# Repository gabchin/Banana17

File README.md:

# Banana17
An RP2040 numpad running QMK

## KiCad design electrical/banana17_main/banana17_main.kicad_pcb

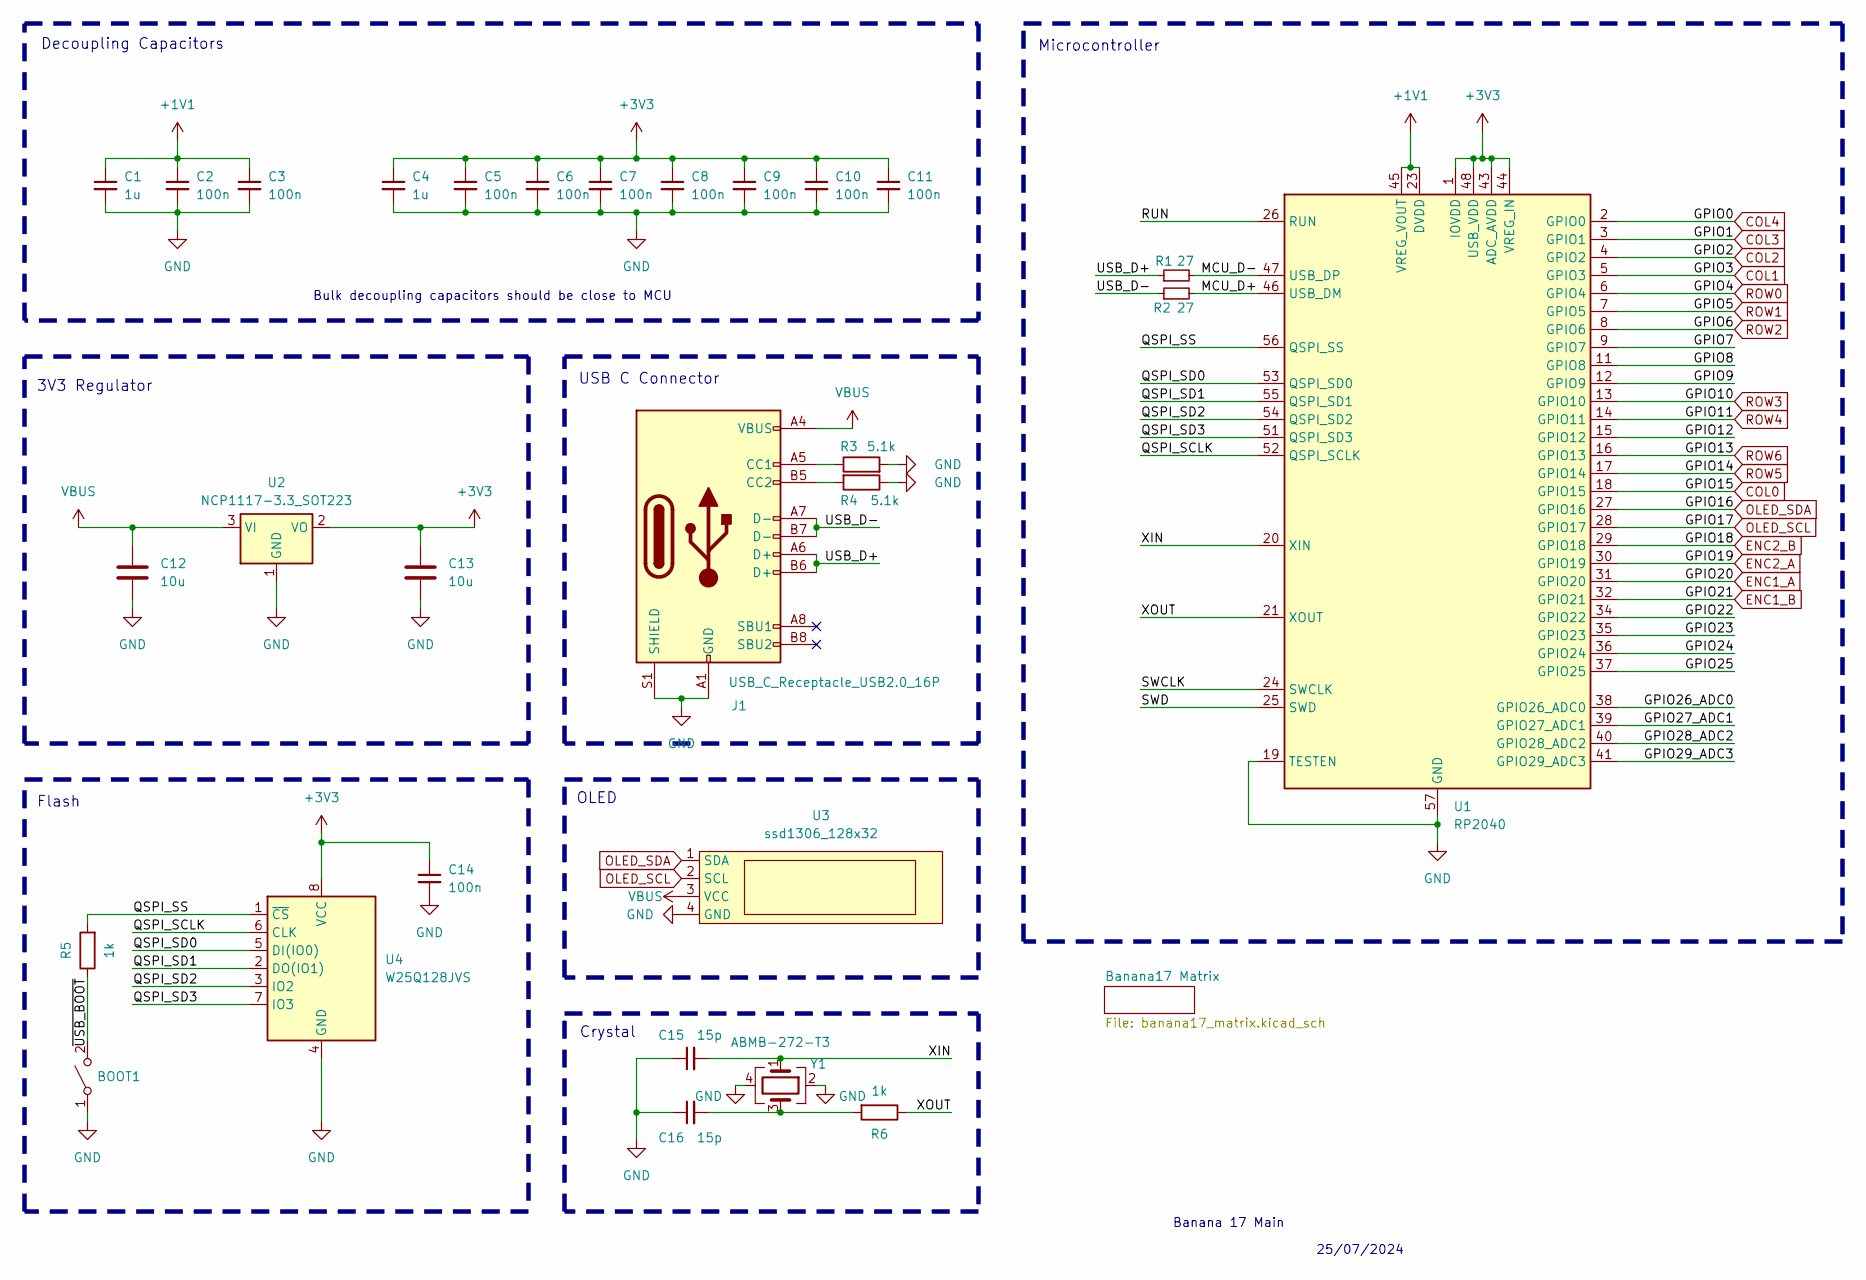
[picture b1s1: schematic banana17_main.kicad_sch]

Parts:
BOOT1: SW_SPST; SW_SPST_PTS810
C1, C4: 1u; C_0402_1005Metric_Pad0.74x0.62mm_HandSolder
C2, C3, C5, C6, C7, C8, C9, C10, C11, C14: 100n; C_0402_1005Metric_Pad0.74x0.62mm_HandSolder
C12, C13: 10u; C_0402_1005Metric_Pad0.74x0.62mm_HandSolder
C15, C16: 15p; C_0402_1005Metric_Pad0.74x0.62mm_HandSolder
J1: USB_C_Receptacle_USB2.0_16P; HRO-TYPE-C-31-M-12-Assembly
R1, R2: 27; R_0402_1005Metric_Pad0.72x0.64mm_HandSolder
R3, R4: 5.1k; R_0402_1005Metric_Pad0.72x0.64mm_HandSolder
R5, R6: 1k; R_0402_1005Metric_Pad0.72x0.64mm_HandSolder
U1: RP2040; QFN-56-1EP_7x7mm_P0.4mm_EP3.2x3.2mm
U2: NCP1117-3.3_SOT223; SOT-223-3_TabPin2
U3: ssd1306_128x32
U4: W25Q128JVS; SOIC-8_5.23x5.23mm_P1.27mm
Y1: ABMB-272-T3; Crystal_SMD_Abracon_ABM8G-4Pin_3.2x2.5mm

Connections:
+1V1: C1.1, C2.1, C3.1, U1.23 (DVDD), U1.45 (VREG_VOUT), U1.50 (DVDD)
+3V3: C4.1, C5.1, C6.1, C7.1, C8.1, C9.1, C10.1, C11.1, C13.1, C14.1, U1.1 (IOVDD), U1.10 (IOVDD), U1.22 (IOVDD), U1.33 (IOVDD), U1.42 (IOVDD), U1.43 (ADC_AVDD), U1.44 (VREG_IN), U1.48 (USB_VDD), U1.49 (IOVDD), U2.2 (VO), U4.8 (VCC)
/GPIO7: U1.9 (GPIO7)
/GPIO8: U1.11 (GPIO8)
/GPIO9: U1.12 (GPIO9)
/GPIO12: U1.15 (GPIO12)
/GPIO22: U1.34 (GPIO22)
/GPIO23: U1.35 (GPIO23)
/GPIO24: U1.36 (GPIO24)
/GPIO25: U1.37 (GPIO25)
/GPIO26_ADC0: U1.38 (GPIO26_ADC0)
/GPIO27_ADC1: U1.39 (GPIO27_ADC1)
/GPIO28_ADC2: U1.40 (GPIO28_ADC2)
/GPIO29_ADC3: U1.41 (GPIO29_ADC3)
/MCU_D+: R2.2, U1.46 (USB_DM)
/MCU_D-: R1.2, U1.47 (USB_DP)
/QSPI_SCLK: U1.52 (QSPI_SCLK), U4.6 (CLK)
/QSPI_SD0: U1.53 (QSPI_SD0), U4.5 (DI(IO0))
/QSPI_SD1: U1.55 (QSPI_SD1), U4.2 (DO(IO1))
/QSPI_SD2: U1.54 (QSPI_SD2), U4.3 (IO2)
/QSPI_SD3: U1.51 (QSPI_SD3), U4.7 (IO3)
/QSPI_SS: R5.2, U1.56 (QSPI_SS), U4.1 (~CS)
/RUN: U1.26 (RUN)
/SWCLK: U1.24 (SWCLK)
/SWD: U1.25 (SWD)
/USB_D+: J1.A6 (D+), J1.B6 (D+), R1.1
/USB_D-: J1.A7 (D-), J1.B7 (D-), R2.1
/XIN: C15.2, U1.20 (XIN), Y1.1
/XOUT: R6.1, U1.21 (XOUT)
/~USB_BOOT: BOOT1.2 (B), R5.1
COL0: U1.18 (GPIO15); also elsewhere on the board
COL1: U1.5 (GPIO3); also elsewhere on the board
COL2: U1.4 (GPIO2); also elsewhere on the board
COL3: U1.3 (GPIO1); also elsewhere on the board
COL4: U1.2 (GPIO0); also elsewhere on the board
ENC1_A: U1.31 (GPIO20); also elsewhere on the board
ENC1_B: U1.32 (GPIO21); also elsewhere on the board
ENC2_A: U1.30 (GPIO19); also elsewhere on the board
ENC2_B: U1.29 (GPIO18); also elsewhere on the board
GND: BOOT1.1 (A), C1.2, C2.2, C3.2, C4.2, C5.2, C6.2, C7.2, C8.2, C9.2, C10.2, C11.2, C12.2, C13.2, C14.2, C15.1, C16.1, J1.A1 (GND), J1.A12 (GND), J1.B1 (GND), J1.B12 (GND), J1.S1 (SHIELD), R3.2, R4.1, U1.19 (TESTEN), U1.57 (GND), U2.1 (GND), U3.4 (GND), U4.4 (GND), Y1.2, Y1.4; also elsewhere on the board
unnamed: C16.2, R6.2, Y1.3
unnamed: J1.A5 (CC1), R3.1
unnamed: J1.B5 (CC2), R4.2
OLED_SCL: U1.28 (GPIO17), U3.2 (SCL)
OLED_SDA: U1.27 (GPIO16), U3.1 (SDA)
ROW0: U1.6 (GPIO4); also elsewhere on the board
ROW1: U1.7 (GPIO5); also elsewhere on the board
ROW2: U1.8 (GPIO6); also elsewhere on the board
ROW3: U1.13 (GPIO10); also elsewhere on the board
ROW4: U1.14 (GPIO11); also elsewhere on the board
ROW5: U1.17 (GPIO14); also elsewhere on the board
ROW6: U1.16 (GPIO13); also elsewhere on the board
VBUS: C12.1, J1.A4 (VBUS), J1.A9 (VBUS), J1.B4 (VBUS), J1.B9 (VBUS), U2.3 (VI), U3.3 (VCC)

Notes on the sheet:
OLED
Decoupling Capacitors
25/07/2024
Banana 17 Main
Crystal
Microcontroller
USB C Connector
Bulk decoupling capacitors should be close to MCU
Flash
3V3 Regulator

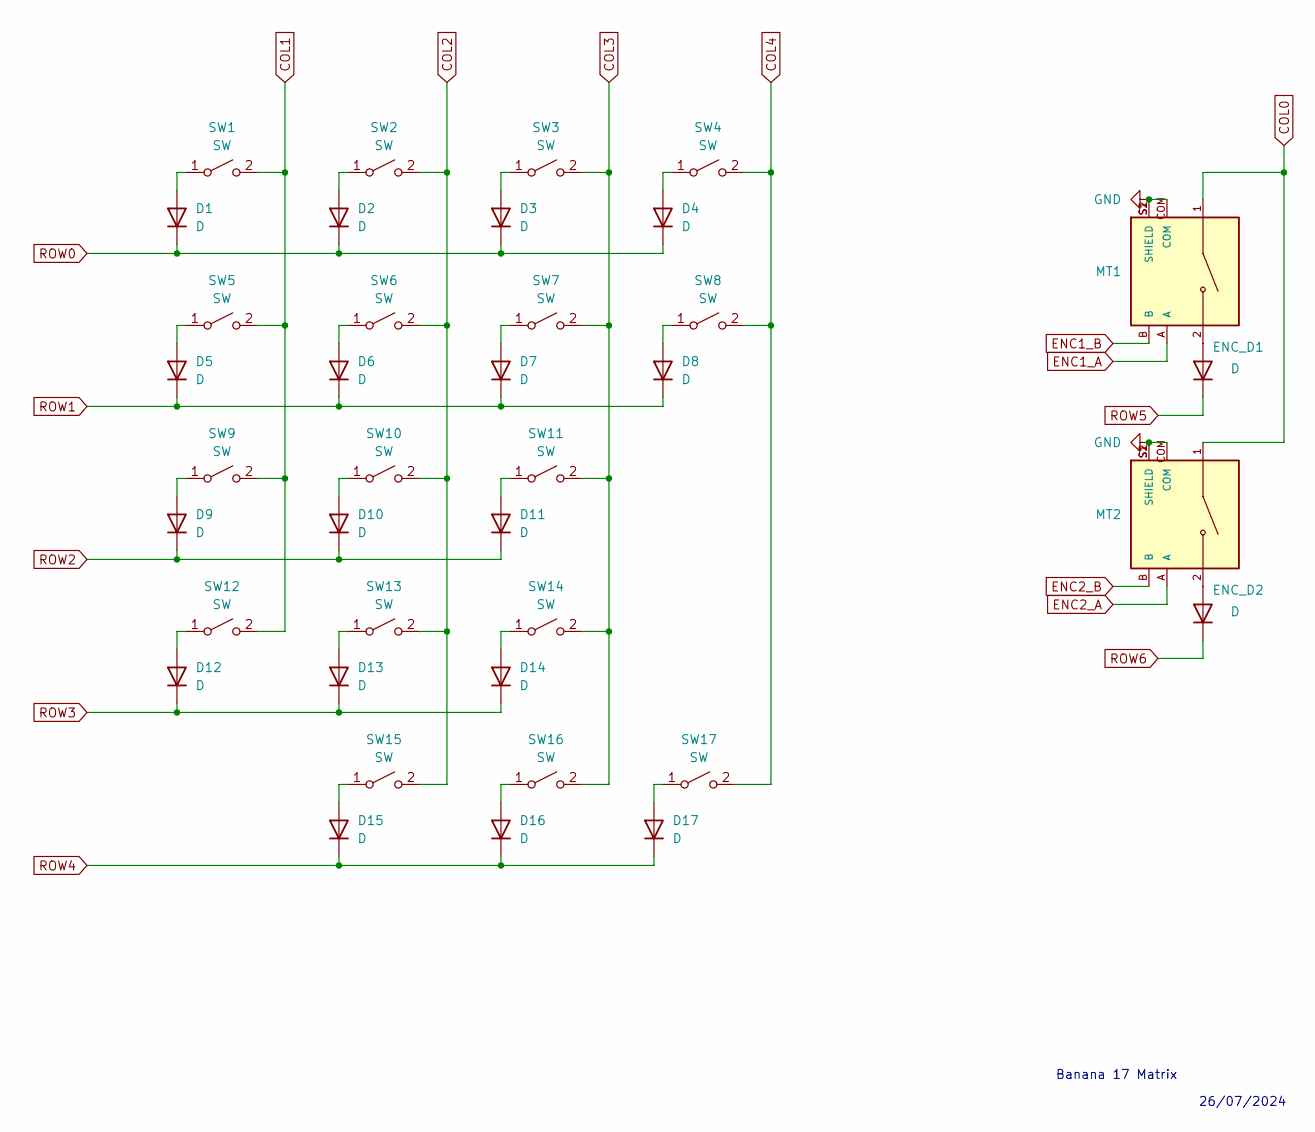
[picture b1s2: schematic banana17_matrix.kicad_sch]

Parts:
D1, D2, D3, D4, D5, D6, D7, D8, D9, D10, D11, D12, D13, D14, D15, D16, D17: D; D_0805_2012Metric_Pad1.15x1.40mm_HandSolder
ENC_D1, ENC_D2: D; D_0805_2012Metric_Pad1.15x1.40mm_HandSolder
MT1, MT2: PEC11R-4215F-S0024; XDCR_PEC11R-4215F-S0024; PARTREV Rev. 09/19
SW1, SW2, SW3, SW4, SW5, SW6, SW7, SW9, SW10, SW11, SW12, SW13, SW14, SW16: SW; MX-Hotswap-1U
SW8, SW17: SW; MX-Hotswap-2U-Vertical
SW15: SW; MX-Hotswap-2U-ReversedStabilizers

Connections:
COL0: MT1.1, MT2.1; also elsewhere on the board
COL1: SW1.2 (B), SW5.2 (B), SW9.2 (B), SW12.2 (B); also elsewhere on the board
COL2: SW2.2 (B), SW6.2 (B), SW10.2 (B), SW13.2 (B), SW15.2 (B); also elsewhere on the board
COL3: SW3.2 (B), SW7.2 (B), SW11.2 (B), SW14.2 (B), SW16.2 (B); also elsewhere on the board
COL4: SW4.2 (B), SW8.2 (B), SW17.2 (B); also elsewhere on the board
ENC1_A: MT1.A; also elsewhere on the board
ENC1_B: MT1.B; also elsewhere on the board
ENC2_A: MT2.A; also elsewhere on the board
ENC2_B: MT2.B; also elsewhere on the board
GND: MT1.COM, MT1.S1 (SHIELD), MT1.S2 (SHIELD), MT2.COM, MT2.S1 (SHIELD), MT2.S2 (SHIELD); also elsewhere on the board
unnamed: D1.2 (A), SW1.1 (A)
unnamed: D2.2 (A), SW2.1 (A)
unnamed: D3.2 (A), SW3.1 (A)
unnamed: D4.2 (A), SW4.1 (A)
unnamed: D5.2 (A), SW5.1 (A)
unnamed: D6.2 (A), SW6.1 (A)
unnamed: D7.2 (A), SW7.1 (A)
unnamed: D8.2 (A), SW8.1 (A)
unnamed: D9.2 (A), SW9.1 (A)
unnamed: D10.2 (A), SW10.1 (A)
unnamed: D11.2 (A), SW11.1 (A)
unnamed: D12.2 (A), SW12.1 (A)
unnamed: D13.2 (A), SW13.1 (A)
unnamed: D14.2 (A), SW14.1 (A)
unnamed: D15.2 (A), SW15.1 (A)
unnamed: D16.2 (A), SW16.1 (A)
unnamed: D17.2 (A), SW17.1 (A)
unnamed: ENC_D1.2 (A), MT1.2
unnamed: ENC_D2.2 (A), MT2.2
ROW0: D1.1 (K), D2.1 (K), D3.1 (K), D4.1 (K); also elsewhere on the board
ROW1: D5.1 (K), D6.1 (K), D7.1 (K), D8.1 (K); also elsewhere on the board
ROW2: D9.1 (K), D10.1 (K), D11.1 (K); also elsewhere on the board
ROW3: D12.1 (K), D13.1 (K), D14.1 (K); also elsewhere on the board
ROW4: D15.1 (K), D16.1 (K), D17.1 (K); also elsewhere on the board
ROW5: ENC_D1.1 (K); also elsewhere on the board
ROW6: ENC_D2.1 (K); also elsewhere on the board

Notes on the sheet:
26/07/2024
Banana 17 Matrix

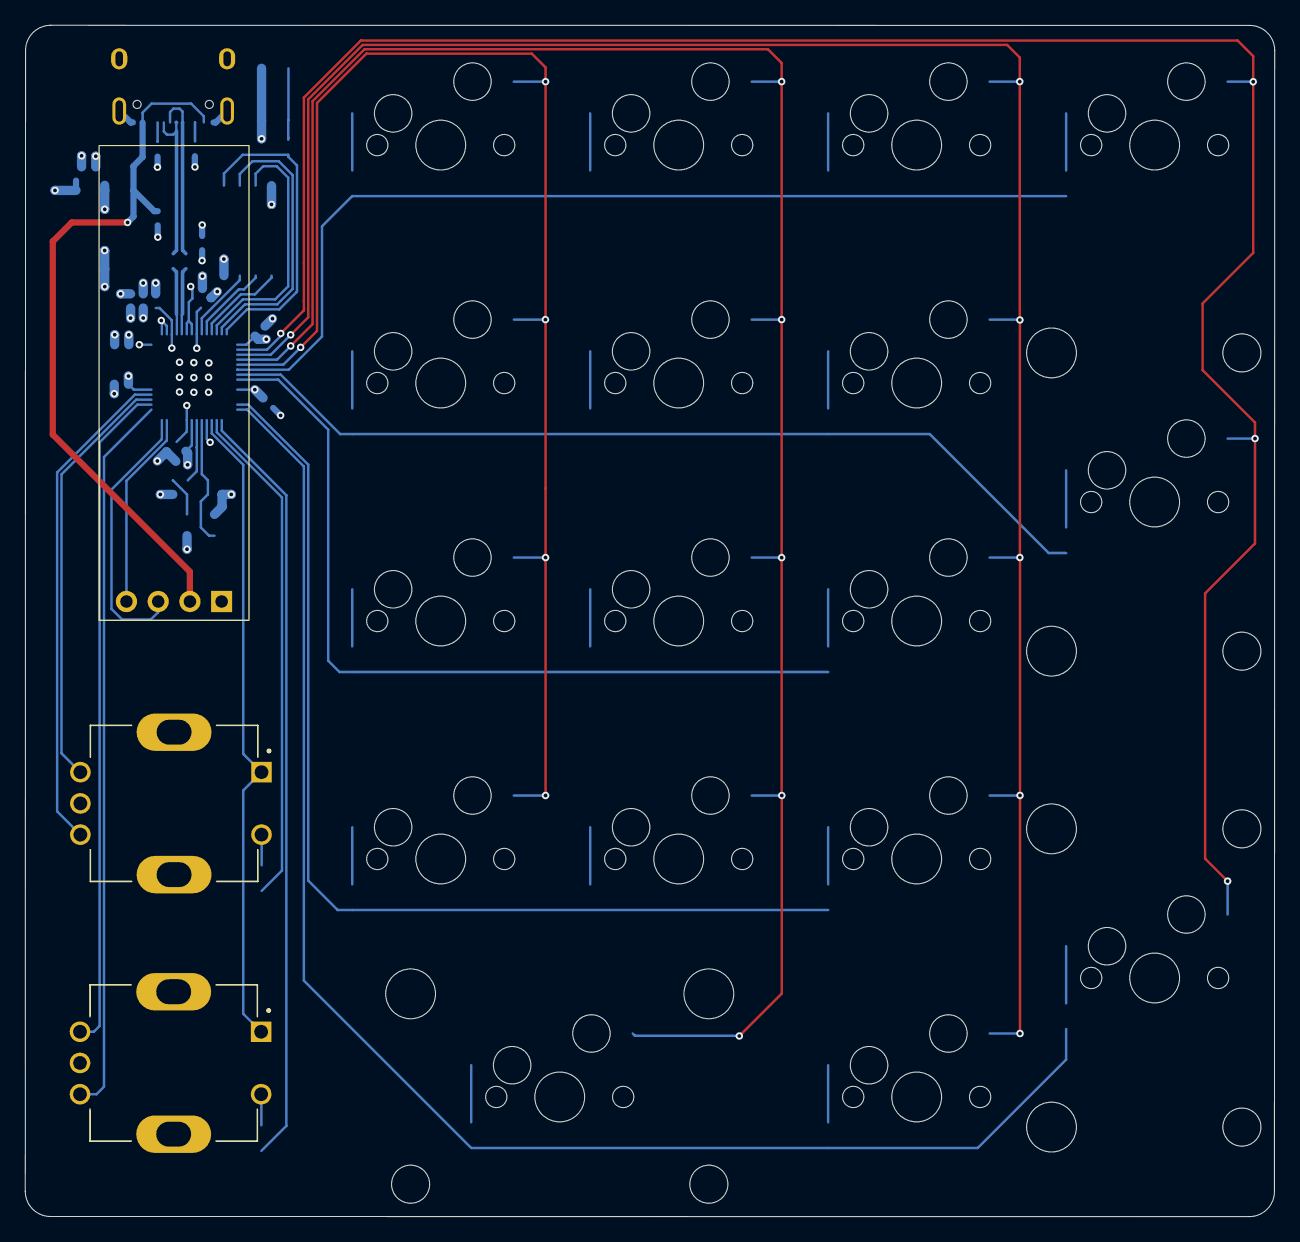
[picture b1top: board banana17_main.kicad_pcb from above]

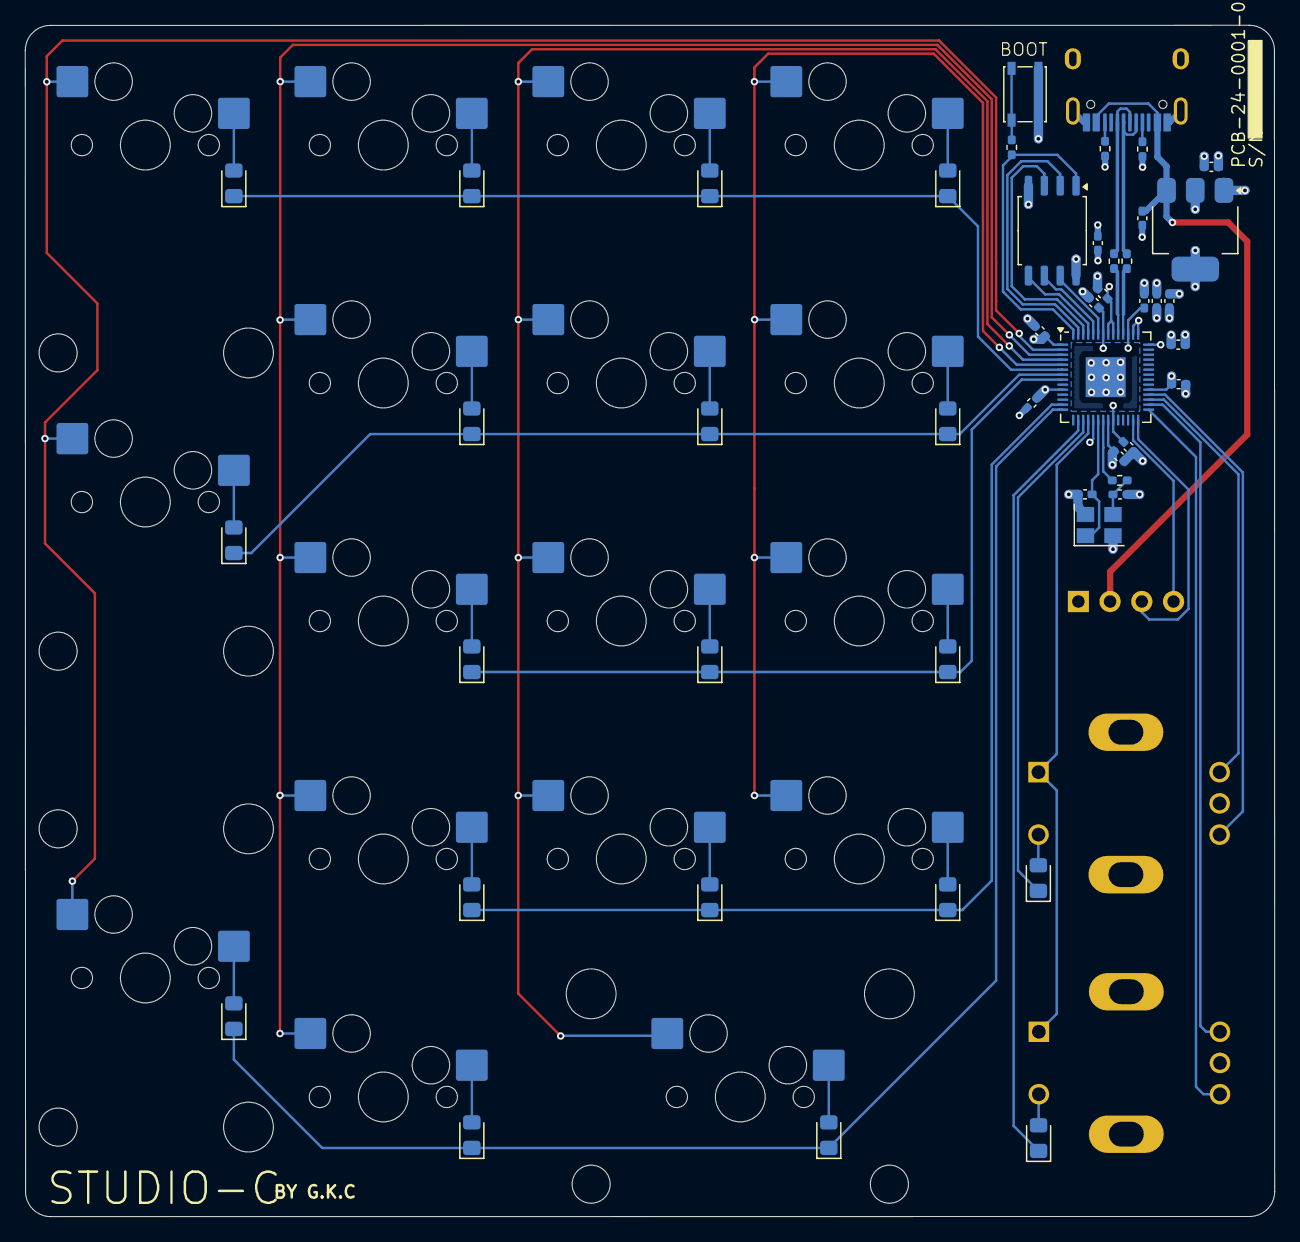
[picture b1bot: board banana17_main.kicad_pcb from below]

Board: 4 copper layers, 100.0 x 95.4 mm, 67 parts (47 on the bottom side), 57 nets.

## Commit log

2024-07-25 Functional keymap with 3 buttons and a rotary encoder
    Importing a functional keymap with 3 buttons and a rotary encoder from previous tests.
2024-07-25 Create KiCAD project for main board
    Create KiCAD project for main board.
2024-07-25 Upload rp2040 datasheet
    Upload rp2040 datasheet.
2024-07-25 RP2040 circuit nearly finished.
    RP2040 circuit nearly finished. Need to add Molex EZ mate connector for UDB support.
2024-07-26 RP2040 minimal circuit complete. Pico EZmate connector added for UDB
    RP2040 minimal circuit complete. Pico EZmate connector added for UDB.
2024-07-26 Created child sheet for keyboard matrix.
    Created child sheet for keyboard matrix.
2024-07-26 Matrix schematic complete
    Matrix schematic complete.
2024-07-26 Altered encoder placement on schematic.
    Altered encoder placement on schematic.
2024-07-26 Uploaded library for SSD1306 128x32.
    Uploaded library for SSD1306 128x32. This needs to be tested first prior to usage.
2024-07-28 Reverted change for SSD1306 library import.
    Reverted change for SSD1306 library import.
2024-07-28 SSD1306 symbol and footprint completed and wired up.
    SSD1306 symbol and footprint completed and wired up.
2024-07-28 Initial footprint all selected. Schematic capture complete.
    Initial footprint all selected. Schematic capture complete.
2024-07-29 MX footprint updated with hotswappable socket.
    MX footprint updated with hotswappable socket. Some issues with KiCAD plugin for keyboard layout editor, switches not aligning.
2024-07-29 Switches positioned in matrix. Working on positioning the RP2040.
    Switches positioned in matrix. Working on positioning the RP2040.
2024-07-29 Minor changes to placement of MCU.
    Minor changes to placement of MCU.
2024-07-29 General layout complete.
    General layout complete.
2024-07-31 Added second rotary encoder.
    Added second rotary encoder.
2024-08-01 RP2040 routed.
    RP2040 routed.
2024-08-01 Incorporated USB C connector. Shrunk overall design.
    Incorporated USB C connector. Shrunk overall design.
2024-08-05 Preliminary matrix complete. Need to do encoders next.
    Preliminary matrix complete. Need to do encoders next.
2024-08-07 Initial PCB complete.
    Initial PCB complete.
2024-08-07 Incorporated switch step files.
    Incorporated switch step files.
2024-08-07 More changes.
    More changes.
2024-08-07 All traces have been drawn. PCB review complete. See description for info.
    PCB Review Comments:
    1. Should use 4 layers for splitting the 1v1 and 3v3 better and reducing loop from matrix
    - Signal
    - GND
    - Split Plane
    - Signal
2024-08-08 Additional changes to routing from DRC.
    Additional changes to routing from DRC.
2024-08-09 Ready for production.
    Ready for production.
2024-08-11 Updated board constraints and stackup.
    Updated board constraints and stackup.
2024-08-11 Split plane complete.
    Split plane complete.
2024-08-11 Differential pair complete. Gerber files plotted.
    Differential pair complete. Gerber files plotted.
2024-08-11 Gerber zip updated.
    Gerber zip updated.
2024-08-11 Final changes.
    Final changes.
2024-08-13 Increased width to accomodate for encoder knobs.
    Increased width to accomodate for encoder knobs.
2024-08-20 Reduce PCB size less than 100mm x 100m for cheaper PCB.
    Reduce PCB size less than 100mm x 100m for cheaper PCB.
2024-08-20 Rerouting matrix.
    Rerouting matrix.
2024-08-20 Additional changes to routing.
    Additional changes to routing.
2024-08-21 Tracks rerouted.
    Tracks rerouted.
2024-08-21 Additional changes.
    Additional changes.
